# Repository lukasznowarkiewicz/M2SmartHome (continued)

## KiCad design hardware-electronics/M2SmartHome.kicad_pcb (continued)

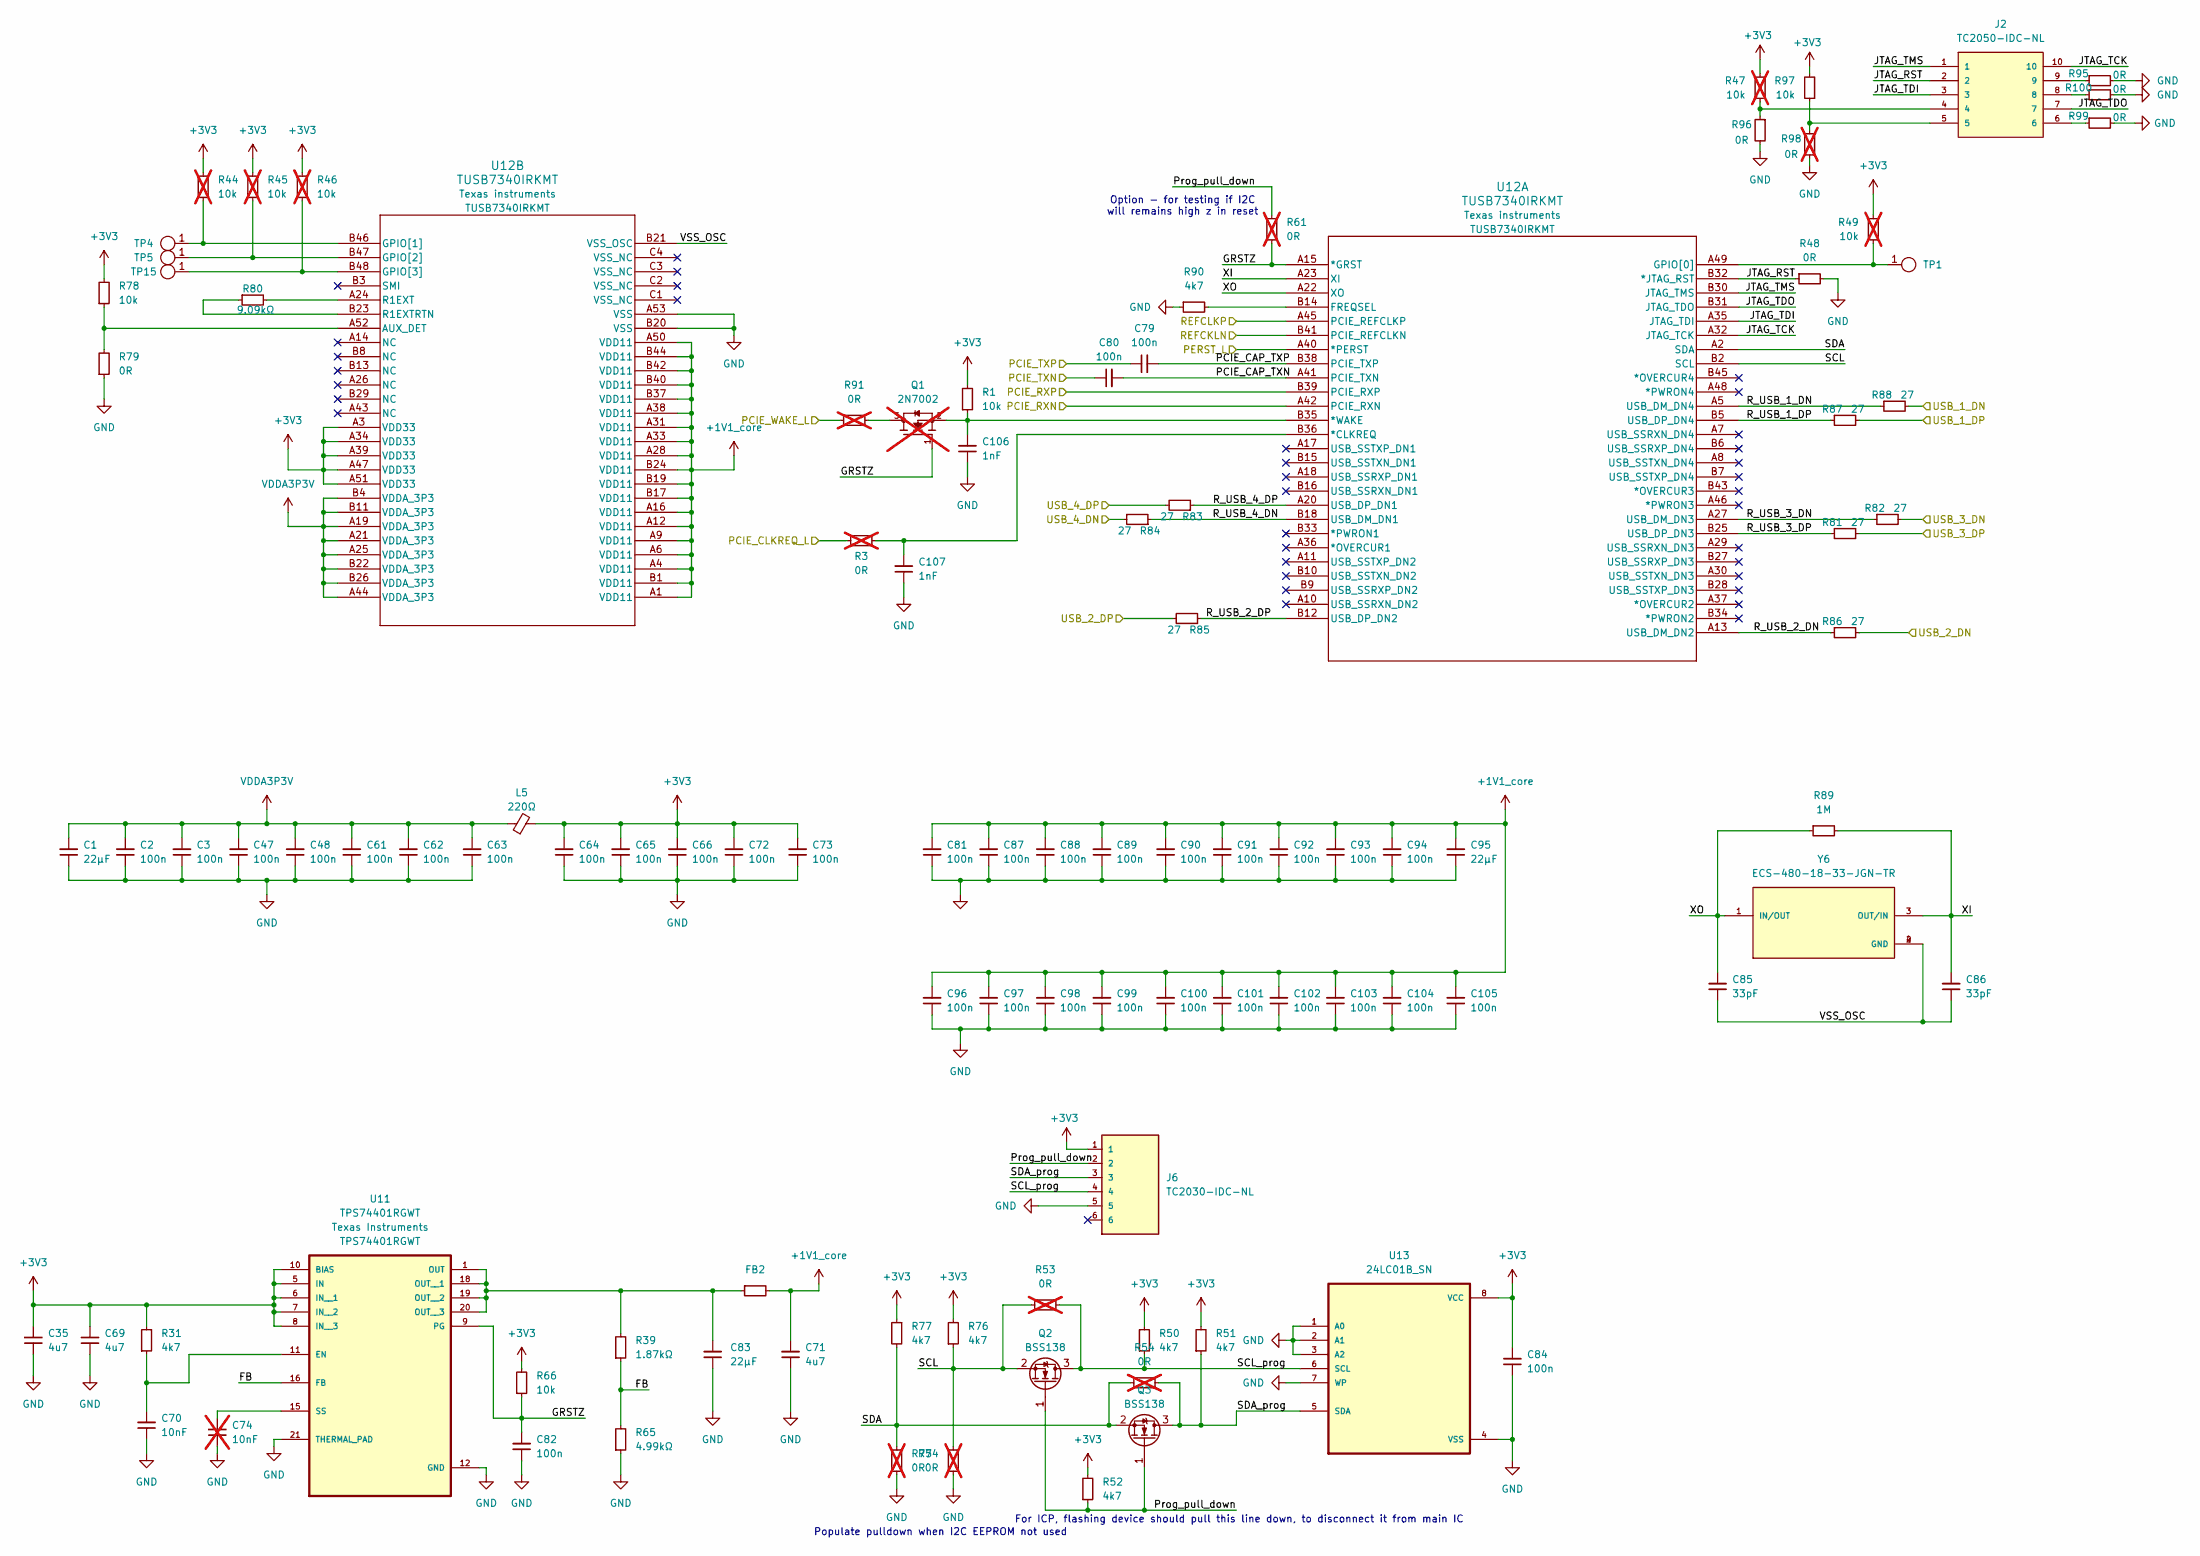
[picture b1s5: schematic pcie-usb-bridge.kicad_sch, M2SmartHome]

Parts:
C1, C83, C95: C_22uF_10pct_10V_0603_C1608X5R1A226M080AC; C_0603; MPN C1608X5R1A226M080AC
C2, C3, C47, C48, C61, C62, C63, C64, C65, C66, C72, C73, C79, C80, C81, C82, C84, C87, C88, C89, C90, C91, C92, C93, C94, C96, C97, C98, C99, C100, C101, C102, C103, C104, C105: C_100n_0402; C_0402; Voltage 10V; MPN GRM155R61A104KA01D
C35, C69, C71: C_4u7_0402; C_0402; Voltage 6.3V; MPN GRM155R60J475ME47D
C70: C_10nF_5pct_50V_0402_C0402C103J5RACTU; C_0402; MPN C0402C103J5RACTU
C74: C_10nF_5pct_50V_0402_C0402C103J5RACTU; C_0402; MPN C0402C103J5RACTU; not fitted
C85, C86: C_33pF_5pct_50V_0402_C1005NP01H330J050BA; C_0402; MPN C1005NP01H330J050BA
C106, C107: C_1nF_10pct_25V_0402_ KGM05AR71E102KH; C_0402; MPN KGM05AR71E102KH
FB2: FB_120R_0603; FB_0603; MPN BLM18AG121SN1D
J2: TC2050-IDC-NL; TAG-CONNECT_TC2050-IDC-NL; PARTREV A
J6: TC2030-IDC-NL; TAG_TC2030-IDC-NL; PARTREV MS
L5: FB_220Ohm_600mA_0805_BLM21PG221SN1D; FB_0805; MPN BLM21PG221SN1D
Q1: 2N7002; TRANS_2N7002; PARTREV 2023-01-11; not fitted
Q2, Q3: BSS138; SOT-23
R1, R66, R78, R97: R_10k_0402; R_0402; Tolerance 1%; MPN CRCW040210K0FKED
R3, R53, R54, R61, R74, R75, R91, R98: R_0_0402; R_0402; MPN CRCW04020000Z0ED; not fitted
R31, R50, R51, R52, R76, R77, R90: R_4k7_0402; R_0402; Tolerance 1%; MPN CRCW04024K70FKED
R39: R_1k87_1pct_0402_CRCW04021K87FKED; R_0402; MPN CRCW04021K87FKED
R44, R45, R46, R47, R49: R_10k_0402; R_0402; Tolerance 1%; MPN CRCW040210K0FKED; not fitted
R48, R79, R95, R96, R99, R100: R_0_0402; R_0402; MPN CRCW04020000Z0ED
R65: R_4k99_1pct_125mW_0402_CRCW04024K99FKEDHP; R_0402; MPN CRCW04024K99FKEDHP
R80: R_9k09_1pct_0402_CRCW04029K09FKED; R_0402; MPN CRCW04029K09FKED
R81, R82, R83, R84, R85, R86, R87, R88: R_27_0402; R_0402; Tolerance 1%; MPN CRCW040227R0FKED
R89: R_1M_0402; R_0402; Tolerance 1%; MPN CRCW04021M00FKED
TP1, TP4, TP5, TP15: TestPoint_Pad_D1.0mm
U11: TPS74401RGWT; MPN TPS74401RGWT
U12: TUSB7340IRKMT; MPN TUSB7340IRKMT
U13: 24LC01B_SN; MPN 24LC01B/SN
Y6: ECS-480-18-33-JGN-TR; MPN ECS-480-18-33-JGN-TR

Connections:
+1V1_core: C71.2, C81.2, C87.2, C88.2, C89.2, C90.2, C91.2, C92.2, C93.2, C94.2, C95.2, C96.2, C97.2, C98.2, C99.2, C100.2, C101.2, C102.2, C103.2, C104.2, C105.2, FB2.2, U12.A1 (VDD11), U12.A4 (VDD11), U12.A6 (VDD11), U12.A9 (VDD11), U12.A12 (VDD11), U12.A16 (VDD11), U12.A28 (VDD11), U12.A31 (VDD11), U12.A33 (VDD11), U12.A38 (VDD11), U12.A50 (VDD11), U12.B1 (VDD11), U12.B17 (VDD11), U12.B19 (VDD11), U12.B24 (VDD11), U12.B37 (VDD11), U12.B40 (VDD11), U12.B42 (VDD11), U12.B44 (VDD11)
+3V3: C35.2, C64.2, C65.2, C66.2, C69.2, C72.2, C73.2, C84.2, J6.1, L5.2, R1.2, R31.2, R44.2, R45.2, R46.2, R47.2, R49.2, R50.2, R51.2, R52.2, R66.2, R76.2, R77.1, R78.2, R97.2, U11.5 (IN), U11.6 (IN__1), U11.7 (IN__2), U11.8 (IN__3), U11.10 (BIAS), U12.A3 (VDD33), U12.A34 (VDD33), U12.A39 (VDD33), U12.A47 (VDD33), U12.A51 (VDD33), U13.8 (VCC); also elsewhere on the board
/PCIE.REFCLKN: U12.B41 (PCIE_REFCLKN); also elsewhere on the board
/PCIE.REFCLKP: U12.A45 (PCIE_REFCLKP); also elsewhere on the board
/PCIE.RXN: U12.A42 (PCIE_RXN); also elsewhere on the board
/PCIE.RXP: U12.B39 (PCIE_RXP); also elsewhere on the board
/PCIE.TXN: C80.1; also elsewhere on the board
/PCIE.TXP: C79.1; also elsewhere on the board
/emmc/USB_1_DN: R88.2; also elsewhere on the board
/emmc/USB_1_DP: R87.2; also elsewhere on the board
/pcie-usb-bridge/FB: R39.1, R65.2, U11.16 (FB)
/pcie-usb-bridge/GRSTZ: C82.2, Q1.1, R61.2, R66.1, U11.9 (PG), U12.A15 (*GRST)
/pcie-usb-bridge/JTAG_RST: J2.2, R48.1, U12.B32 (*JTAG_RST)
/pcie-usb-bridge/JTAG_TCK: J2.10, U12.A32 (JTAG_TCK)
/pcie-usb-bridge/JTAG_TDI: J2.3, U12.A35 (JTAG_TDI)
/pcie-usb-bridge/JTAG_TDO: J2.7, U12.B31 (JTAG_TDO)
/pcie-usb-bridge/JTAG_TMS: J2.1, U12.B30 (JTAG_TMS)
/pcie-usb-bridge/PCIE_CAP_TXN: C80.2, U12.A41 (PCIE_TXN)
/pcie-usb-bridge/PCIE_CAP_TXP: C79.2, U12.B38 (PCIE_TXP)
/pcie-usb-bridge/PCIE_CLKREQ_L: R3.1; also elsewhere on the board
/pcie-usb-bridge/PCIE_WAKE_L: R91.1; also elsewhere on the board
/pcie-usb-bridge/PERST_L: U12.A40 (*PERST); also elsewhere on the board
/pcie-usb-bridge/Prog_pull_down: J6.2, Q2.1 (G), Q3.1 (G), R52.1, R61.1
/pcie-usb-bridge/R_USB_1_DN: R88.1, U12.A5 (USB_DM_DN4)
/pcie-usb-bridge/R_USB_1_DP: R87.1, U12.B5 (USB_DP_DN4)
/pcie-usb-bridge/R_USB_2_DN: R86.1, U12.A13 (USB_DM_DN2)
/pcie-usb-bridge/R_USB_2_DP: R85.1, U12.B12 (USB_DP_DN2)
/pcie-usb-bridge/R_USB_3_DN: R82.1, U12.A27 (USB_DM_DN3)
/pcie-usb-bridge/R_USB_3_DP: R81.1, U12.B25 (USB_DP_DN3)
/pcie-usb-bridge/R_USB_4_DN: R84.1, U12.B18 (USB_DM_DN1)
/pcie-usb-bridge/R_USB_4_DP: R83.1, U12.A20 (USB_DP_DN1)
/pcie-usb-bridge/SCL: Q2.2 (S), R53.2, R74.2, R76.1, U12.B2 (SCL)
/pcie-usb-bridge/SCL_prog: J6.4, Q2.3 (D), R50.1, R53.1, U13.6 (SCL)
/pcie-usb-bridge/SDA: Q3.2 (S), R54.2, R75.2, R77.2, U12.A2 (SDA)
/pcie-usb-bridge/SDA_prog: J6.3, Q3.3 (D), R51.1, R54.1, U13.5 (SDA)
/pcie-usb-bridge/USB_2_DN: R86.2; also elsewhere on the board
/pcie-usb-bridge/USB_2_DP: R85.2; also elsewhere on the board
/pcie-usb-bridge/USB_3_DN: R82.2; also elsewhere on the board
/pcie-usb-bridge/USB_3_DP: R81.2; also elsewhere on the board
/pcie-usb-bridge/USB_4_DN: R84.2; also elsewhere on the board
/pcie-usb-bridge/USB_4_DP: R83.2; also elsewhere on the board
/pcie-usb-bridge/VSS_OSC: C85.1, C86.1, U12.B21 (VSS_OSC), Y6.2 (GND), Y6.4 (GND)
/pcie-usb-bridge/XI: C86.2, R89.2, U12.A23 (XI), Y6.3 (OUT/IN)
/pcie-usb-bridge/XO: C85.2, R89.1, U12.A22 (XO), Y6.1 (IN/OUT)
GND: C1.1, C2.1, C3.1, C35.1, C47.1, C48.1, C61.1, C62.1, C63.1, C64.1, C65.1, C66.1, C69.1, C70.1, C71.1, C72.1, C73.1, C74.1, C81.1, C82.1, C83.1, C84.1, C87.1, C88.1, C89.1, C90.1, C91.1, C92.1, C93.1, C94.1, C95.1, C96.1, C97.1, C98.1, C99.1, C100.1, C101.1, C102.1, C103.1, C104.1, C105.1, C106.1, C107.1, J6.5, R48.2, R65.1, R74.1, R75.1, R79.1, R90.1, R95.2, R96.2, R98.2, R99.2, R100.2, U11.12 (GND), U11.21 (THERMAL_PAD), U12.A53 (VSS), U12.B20 (VSS), U13.1 (A0), U13.2 (A1), U13.3 (A2), U13.4 (VSS), U13.7 (WP); also elsewhere on the board
unnamed: J2.4, R47.1, R96.1
unnamed: J2.5, R97.1, R98.1
unnamed: J2.6, R99.1
unnamed: J2.8, R100.1
unnamed: J2.9, R95.1
unnamed: Q1.3, R91.2
unnamed: C70.2, R31.1, U11.11 (EN)
unnamed: C83.2, FB2.1, R39.2, U11.1 (OUT), U11.18 (OUT__1), U11.19 (OUT__2), U11.20 (OUT__3)
unnamed: C74.2, U11.15 (SS)
unnamed: C107.2, R3.2, U12.B36 (*CLKREQ)
unnamed: C106.2, Q1.2, R1.1, U12.B35 (*WAKE)
unnamed: R90.2, U12.B14 (FREQSEL)
unnamed: R49.1, TP1.1, U12.A49 (GPIO[0])
unnamed: R78.1, R79.2, U12.A52 (AUX_DET)
unnamed: R44.1, TP4.1, U12.B46 (GPIO[1])
unnamed: R45.1, TP5.1, U12.B47 (GPIO[2])
unnamed: R46.1, TP15.1, U12.B48 (GPIO[3])
unnamed: R80.2, U12.A24 (R1EXT)
unnamed: R80.1, U12.B23 (R1EXTRTN)
VDDA3P3V: C1.2, C2.2, C3.2, C47.2, C48.2, C61.2, C62.2, C63.2, L5.1, U12.A19 (VDDA_3P3), U12.A21 (VDDA_3P3), U12.A25 (VDDA_3P3), U12.A44 (VDDA_3P3), U12.B4 (VDDA_3P3), U12.B11 (VDDA_3P3), U12.B22 (VDDA_3P3), U12.B26 (VDDA_3P3)

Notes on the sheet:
For ICP, flashing device should pull this line down, to disconnect it from main IC
Populate pulldown when I2C EEPROM not used
Option - for testing if I2C will remains high z in reset

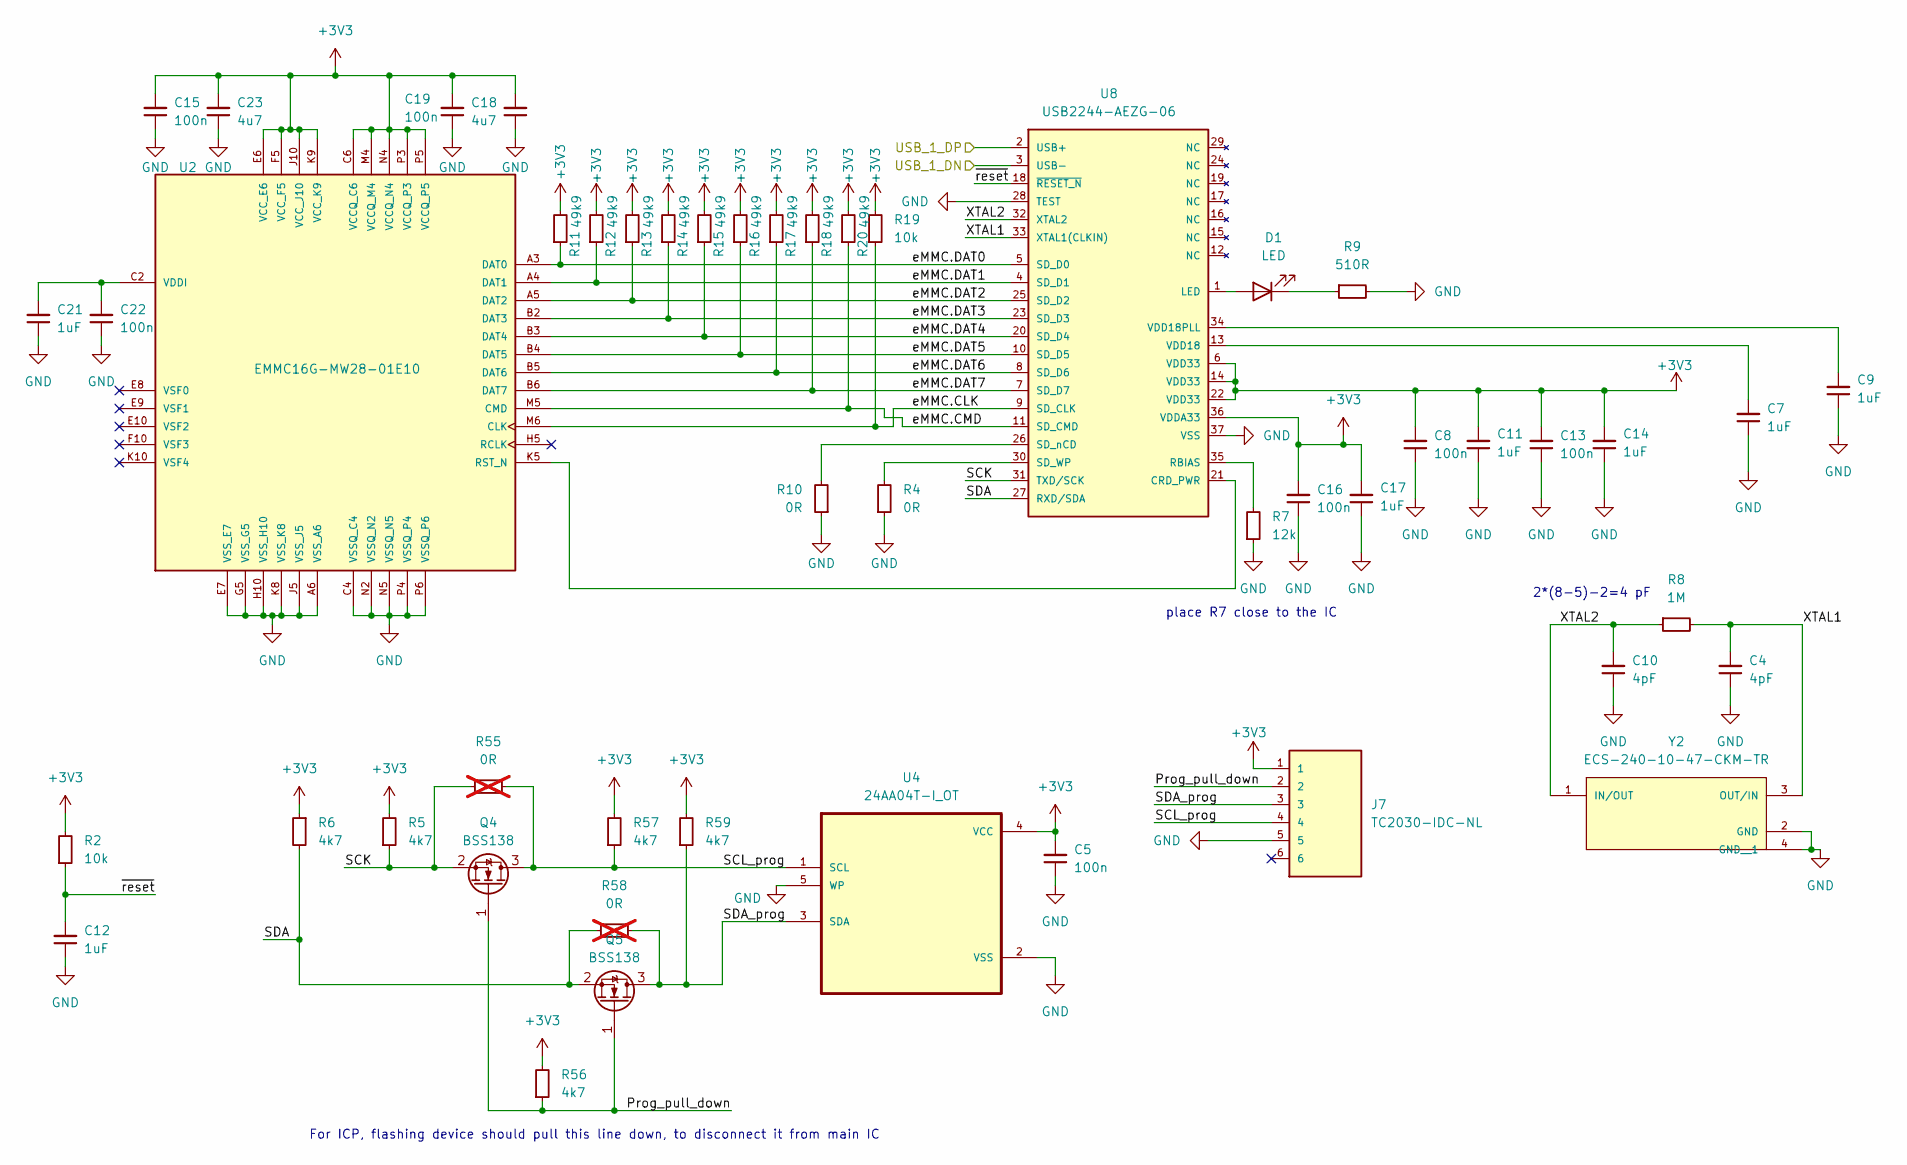
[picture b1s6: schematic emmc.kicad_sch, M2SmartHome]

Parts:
C4, C10: C_4pF_0402; C_0402; Voltage 50V; MPN GRM1555C1H4R0CA01D
C5, C8, C13, C15, C16, C19, C22: C_100n_0402; C_0402; Voltage 10V; MPN GRM155R61A104KA01D
C7, C9, C11, C12, C14, C17, C21: C_1uF_0402; C_0402; Voltage 50V; MPN GRM155R61H105KE05D
C18, C23: C_4u7_0402; C_0402; Voltage 6.3V; MPN GRM155R60J475ME47D
D1: LED; LED_KPT-1608ZGC
J7: TC2030-IDC-NL; TAG_TC2030-IDC-NL; PARTREV MS
Q4, Q5: BSS138; SOT-23
R2, R19: R_10k_0402; R_0402; Tolerance 1%; MPN CRCW040210K0FKED
R4, R10: R_0_0402; R_0402; MPN CRCW04020000Z0ED
R5, R6, R56, R57, R59: R_4k7_0402; R_0402; Tolerance 1%; MPN CRCW04024K70FKED
R7: R_12k_0402; R_0402; Tolerance 1%; Voltage 50V; MPN CRCW040212K0FKTDBC
R8: R_1M_0402; R_0402; Tolerance 1%; MPN CRCW04021M00FKED
R9: R_510R_0402; R_0402; Tolerance 1%; MPN CRCW0402510RJNED
R11, R12, R13, R14, R15, R16, R17, R18, R20: R_49k9_0402; R_0402; Tolerance 1%; MPN CRCW040249K9FKED
R55, R58: R_0_0402; R_0402; MPN CRCW04020000Z0ED; not fitted
U2: EMMC16G-MW28-01E10
U4: 24AA04T-I_OT
U8: USB2244-AEZG-06
Y2: ECS-240-10-47-CKM-TR; PARTREV 2017

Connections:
+3V3: C5.2, C8.2, C11.2, C13.2, C14.2, C15.2, C16.2, C17.2, C18.2, C19.2, C23.2, J7.1, R2.2, R5.2, R6.1, R11.2, R12.2, R13.2, R14.2, R15.2, R16.2, R17.2, R18.2, R19.2, R20.2, R56.2, R57.2, R59.2, U2.C6 (VCCQ_C6), U2.E6 (VCC_E6), U2.F5 (VCC_F5), U2.J10 (VCC_J10), U2.K9 (VCC_K9), U2.M4 (VCCQ_M4), U2.N4 (VCCQ_N4), U2.P3 (VCCQ_P3), U2.P5 (VCCQ_P5), U4.4 (VCC), U8.6 (VDD33), U8.14 (VDD33), U8.22 (VDD33), U8.36 (VDDA33); also elsewhere on the board
/emmc/Prog_pull_down: J7.2, Q4.1 (G), Q5.1 (G), R56.1
/emmc/SCK: Q4.2 (S), R5.1, R55.2, U8.31 (TXD/SCK)
/emmc/SCL_prog: J7.4, Q4.3 (D), R55.1, R57.1, U4.1 (SCL)
/emmc/SDA: Q5.2 (S), R6.2, R58.2, U8.27 (RXD/SDA)
/emmc/SDA_prog: J7.3, Q5.3 (D), R58.1, R59.1, U4.3 (SDA)
/emmc/USB_1_DN: U8.3 (USB-); also elsewhere on the board
/emmc/USB_1_DP: U8.2 (USB+); also elsewhere on the board
/emmc/XTAL1: C4.2, R8.2, U8.33 (XTAL1(CLKIN)), Y2.3 (OUT/IN)
/emmc/XTAL2: C10.2, R8.1, U8.32 (XTAL2), Y2.1 (IN/OUT)
/emmc/eMMC.CLK: R19.1, U2.M6 (CLK), U8.9 (SD_CLK)
/emmc/eMMC.CMD: R20.1, U2.M5 (CMD), U8.11 (SD_CMD)
/emmc/eMMC.DAT0: R11.1, U2.A3 (DAT0), U8.5 (SD_D0)
/emmc/eMMC.DAT1: R12.1, U2.A4 (DAT1), U8.4 (SD_D1)
/emmc/eMMC.DAT2: R13.1, U2.A5 (DAT2), U8.25 (SD_D2)
/emmc/eMMC.DAT3: R14.1, U2.B2 (DAT3), U8.23 (SD_D3)
/emmc/eMMC.DAT4: R15.1, U2.B3 (DAT4), U8.20 (SD_D4)
/emmc/eMMC.DAT5: R16.1, U2.B4 (DAT5), U8.10 (SD_D5)
/emmc/eMMC.DAT6: R17.1, U2.B5 (DAT6), U8.8 (SD_D6)
/emmc/eMMC.DAT7: R18.1, U2.B6 (DAT7), U8.7 (SD_D7)
/emmc/~reset: C12.2, R2.1, U8.18 (~RESET_N)
GND: C4.1, C5.1, C7.1, C8.1, C9.1, C10.1, C11.1, C12.1, C13.1, C14.1, C15.1, C16.1, C17.1, C18.1, C19.1, C21.1, C22.1, C23.1, J7.5, R4.1, R7.1, R9.2, R10.1, U2.A6 (VSS_A6), U2.C4 (VSSQ_C4), U2.E7 (VSS_E7), U2.G5 (VSS_G5), U2.H10 (VSS_H10), U2.J5 (VSS_J5), U2.K8 (VSS_K8), U2.N2 (VSSQ_N2), U2.N5 (VSSQ_N5), U2.P4 (VSSQ_P4), U2.P6 (VSSQ_P6), U4.2 (VSS), U4.5 (WP), U8.28 (TEST), U8.37 (VSS), Y2.2 (GND), Y2.4 (GND__1); also elsewhere on the board
unnamed: D1.2 (A), U8.1 (LED)
unnamed: D1.1 (K), R9.1
unnamed: U2.K5 (RST_N), U8.21 (CRD_PWR)
unnamed: C21.2, C22.2, U2.C2 (VDDI)
unnamed: R7.2, U8.35 (RBIAS)
unnamed: R4.2, U8.30 (SD_WP)
unnamed: R10.2, U8.26 (SD_nCD)
unnamed: C7.2, U8.13 (VDD18)
unnamed: C9.2, U8.34 (VDD18PLL)

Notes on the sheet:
For ICP, flashing device should pull this line down, to disconnect it from main IC
2*(8-5)-2=4 pF
place R7 close to the IC

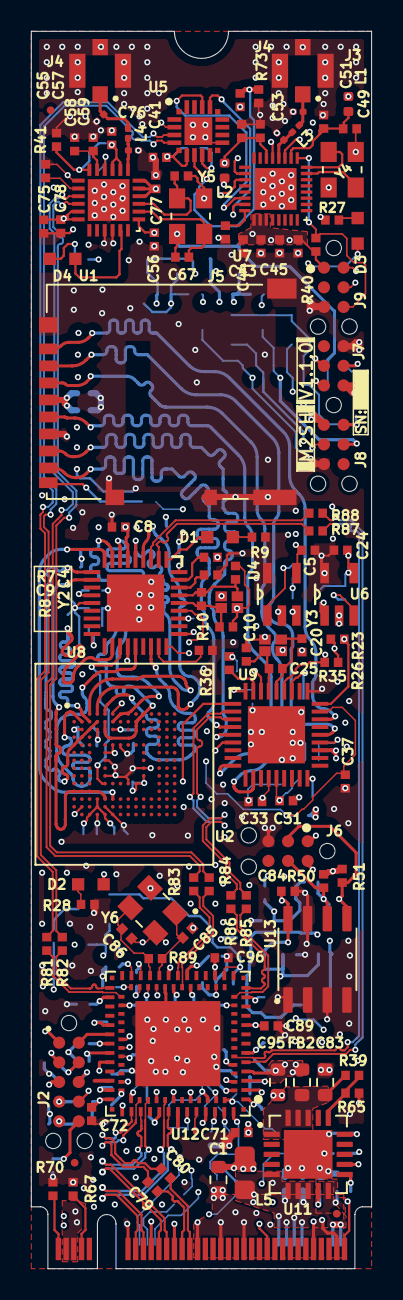
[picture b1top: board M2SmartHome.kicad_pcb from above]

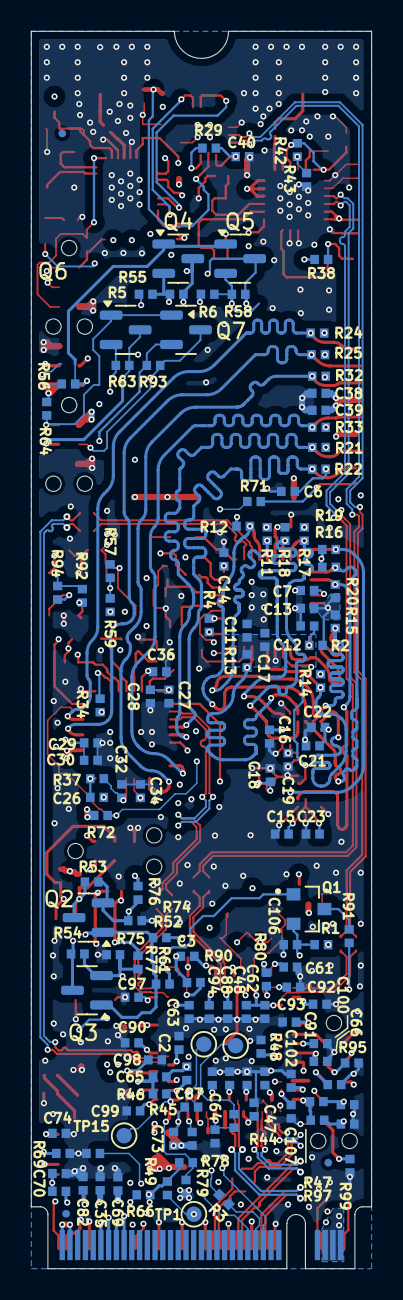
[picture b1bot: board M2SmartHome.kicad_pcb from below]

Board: 6 copper layers, 22.0 x 80.0 mm, 257 parts (143 on the bottom side), 143 nets.

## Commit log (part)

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2024-11-12 [#17] uSD data lines WIP
2024-11-13 [#17] SCH update USB net names
2024-11-13 [#17] uSD components connections
2024-11-13 [#17] Thread radio components connection WIP
2024-11-13 [#17] WiFi radio components connection WIP
2024-11-17 [#17] downsized all vias
2024-11-17 [#17] Chane stackup to JLC04081H-3313
2024-11-17 [#17] USB 2.0 routed for new stackup
2024-11-17 [#17] eMMC routing WIP
2024-11-17 [#17] uSD routing WIP
2024-11-20 [#17] eMMC moved by 0.8 mm
2024-11-20 [#17] eMMC routing after repositioning
2024-11-20 [#17] eMMC controller moved 1mm
2024-11-20 [#17] eMMC controller rerouting tracks after repositioning
2024-11-20 [#17] Resized designators
2024-11-20 [#17] Reposition designators top
2024-11-20 [#17] Reposition designators bottom
2024-11-20 [#17] Update copper planes
2024-11-20 [#17] PCIe bridge DCDC converter routing WI
2024-11-21 [#17] PCIe bridge DCDC converter routing
2024-11-21 [#17] PCIe bridge routing around WIP
2024-11-21 [#17] Moved everything 1 mm away from M.2 connector
2024-11-21 [#17] PCIe bridge routing around
2024-11-21 [#17] PCIe bridge matched lenght of PCIe lines
2024-11-21 [#17] Matched lenght of USB lines
2024-11-21 [#17] Routing uSD data lines WIP
2024-11-21 [#17] uSD data lines lenght matching WIP
2024-11-23 [#17] connecting unconneted nets WIP
2024-11-23 [#17] eMMC routing WIP set proper trace wthicknes to keep SE 50 ohm
2024-11-23 [#17] eMMC routing WIP removed unecessary cap
2024-11-23 [#17] eMMC and uSD routing WIP
2024-11-23 [#17] USB add cutouts and GND planes under resistors to keep impedance
2024-11-24 [#17] uSD lenght matching
2024-11-24 [#17] eMMC lenght matching WIP
2024-11-24 [#17] Change via hole to 0.25 mm
2024-11-24 [#17] WIFI UFL connector routing
2024-11-24 [#17] Thread routing
2024-11-25 [#17] Thread routing WIP
2024-11-25 [#17] USB routing WIP
2024-11-25 [#17] Add GND copper on F and B to equalize copper distrubution
2024-11-25 [#17] Working on power planes
2024-11-25 [#17] Thread routing, power planes
2024-11-25 [#18] SCH excluded ERC violations
2024-11-25 [#20] PCB cleanup WIP
2024-11-25 [#20] PCB DRC WIP
2024-11-25 [#20] PCB DRC WIP ignored all solder mask aperture bridges items with different nets
2024-11-25 [#20] PCB DRC WIP shortened uSD card pads
2024-11-25 [#20] PCB DRC WIP changed minimum track width to 0.1 mm
2024-11-25 [#20] PCB DRC WIP HS fanouts
2024-11-25 [#20] PCB DRC WIP USB lines fix
2024-11-25 [#20] PCB DRC WIP check with JLCPCB viewer
2024-11-26 [#20] PCB DRC warnings WIP excluded all text height violations
2024-11-26 [#20] PCB DRC warnings WIP placing desginators
2024-11-26 [#20] PCB DRC warnings WIP placing desginators, fixing footptints
2024-11-26 [#20] PCB DRC warnings WIP fix missing footprints
2024-11-26 [#20] PCB DRC warnings fix
2024-11-26 [#20] PCB DRC errors under eMMC
2024-11-26 [#20] PCB corrected mounting hole cutour according to PCIe sig specification
2024-11-26 [#20] PCB correct internal planes under edge connector according to figure 97 in PCIe M.2 electromechacnial specification
2024-11-26 [#20] PCB minor corrections
2024-11-26 [#20] PCB excluded DRC errors under eMMC
2024-11-26 [#20] PCB fix unconnected items
2024-11-26 [#20] PCB lenght matching eMMC WIP
2024-11-26 [#20] PCB lenght matched eMMC
2024-11-26 [#20] PCB exclude DRC errors related to eMMC
2024-11-26 [#20] PCB lenght match uSD
2024-11-26 [#20] PCB lenght match USB
2024-11-26 [#20] PCB fix tracks connected to uSD slot
2024-11-26 [#20] PCB add planes cutouts on vias on USB tracks
2024-11-26 [#20] PCB add vias near UFL connectors
2024-11-26 [#20] PCB add cap on pcie bridge pin 33
2024-11-26 [#20] PCB fix track on eMMC memory & fix DRC
2024-11-26 [#20] PCB add pullup filtration cap on uSD datalines
2024-11-26 [#20] PCB fix DRC
2024-11-26 [#20] PCB lenght match fix
2024-11-27 [#20] PCB repour polygons
2024-11-27 [#20] PCB minor fixes
2024-12-01 Add order files
2024-12-01 Add WIP sourcing document - add LCSC parts
2024-12-01 Add WIP sourcing document - add Mouser and Digikey parts
2025-01-14 [#24] Add symbol for TUSB7340IRKMT
2025-01-14 [#24] Add footprint and 3d model for TUSB7340IRKMT
2025-01-14 [#24] Add TUSB7340IRKMT to PCB (mockip)
2025-01-14 [#24] Update TUSB7340IRKMT footprint
2025-01-15 [#24] Add ECS-480-8-33B-CWN-TR
2025-01-15 [#24] Update ECS-480-8-33B-CWN-TR
2025-01-15 [#24] Add TPS74401RGWT
2025-01-15 [#24] Add 24LC01B_SN
2025-01-15 [#24] Add C1608X5R1A226M080AC
2025-01-15 [#24] Add BLM21PG221SN1D
2025-01-15 [#24] Add CRCW04029K09FKED
2025-01-15 [#24] Add CRCW04021K87FKED
2025-01-15 [#24] Add CRCW04024K99FKEDHP
2025-01-15 [#24] Add C0402C103J5RACTU
2025-01-15 [#24] SCH 1V1 LDO WIP
2025-01-15 [#24] SCH 1V1 LDO
2025-01-15 [#24] SCH I2C EEPROM
2025-01-15 [#24] SCH connect power part of TUSB7340IRKMT
2025-01-15 [#24] Add ECS-480-18-33-JGN-TR
2025-01-15 [#24] Add C1005NP01H330J050BA
2025-01-15 [#24] SCH add oscillator for TUSB7340IRKMT
2025-01-15 [#24] SCH add USB connections to TUSB7340IRKMT
2025-01-15 [#24] SCH add PCIe connections to TUSB7340IRKMT
2025-01-25 [#25] Add step model for CONMHF1-SMD-T
2025-01-25 [#25] Add step model for RTL8188FTV-VC-CG
2025-01-25 [#25] Add step model for ABM8-40.000MHZ-B2-T
2025-01-25 [#25] Add step model for ABM8-38.400MHZ-10-D1G-T
2025-01-25 [#25] Add step model for KPT-1608ZGC
2025-01-25 [#25] Add step model for 24AA04T-I/OT
2025-01-25 [#25] Add step model for XTAL_ABM8-12.000MHZ-B2-T
2025-01-25 [#25] Add step model for TPS62822DLCR
2025-01-25 [#25] Add step model for XFL4015-471MEC
2025-01-25 [#25] Update board
2025-01-25 [#25] Update board add missing TPS
2025-01-26 Add renders of the board
2025-01-29 Add assembly render
2025-01-29 Remove old docs export pipeline
2025-01-29 Add renders and image
2025-01-29 Add board views to README
2025-01-29 Add schematic to README
2025-01-29 Describe schematic in README
2025-01-29 Add board renders
2025-01-29 Readme Board bringup - PCIe bridge
2025-01-29 Readme Board bringup - eMMC memory
2025-01-29 Readme Board bringup - uSD reader
2025-01-29 Readme - add rev
2025-01-29 Restore design files from commit 30c85d8
2025-01-29 Add info about develop branch
2025-03-11 [#24] SCH Pcie bridge Cleanup
2025-03-11 [#24] SCH Pcie bridge add power filtration
2025-03-11 [#24] SCH Pcie bridge WAKE and CLKREQ signals
2025-03-12 [#24] SCH Pcie bridge fix footprint paths
2025-03-12 [#24] PCB Pcie bridge placement WIP
2025-03-13 [#24] PCB Pcie bridge placement
2025-03-13 [#24] PCB tag-connect programming connectors brainstorming
2025-03-17 [#26] Correct TX/RX PCIe line swap
2025-03-17 [#26] PCIe routing WIP
2025-03-18 [#26] Changed stackup to 6 layers JLC06081H-2116
2025-03-18 [#26] Update PCIe DP rules
2025-03-18 [#26] Update USB DP rules and ref plane openings
2025-03-18 [#26] Update PCIe DP rules to match 85ohm and ref plane openings
2025-03-18 [#26] Add more Vias under RF chips
2025-03-18 [#26] Add cutout and ref plane under U.FL connectors
2025-03-18 [#26] Fix mounting screw and screwhead opening
2025-03-19 [#26] Fix power planes on internal layers after updating stackup
2025-03-19 [#26] Pcie bridge HS fanout
2025-03-19 [#24] Pcie bridge vias for power supply
2025-03-19 [#24] Pcie bridge oscillator routing
2025-03-19 [#24] Pcie bridge decoupling capacitors routing
2025-03-20 [#26] Remove power plane splits for invidual devices
2025-03-20 [#26] Add programing interface for I2c devices
2025-03-20 [#26] Add programing interface for silicon labs MCU
2025-03-24 [#27] Add BOM for rev 1.1.0
2025-03-24 [#26] Correct MPN GRM155R61A104KA01D
2025-03-24 [#26] Correct MPN GRM155R61H105KE05D
2025-03-24 [#26] Correct MPN GRM1555C1H120GA01D
2025-03-24 [#26] Replace 500ohm to 510ohm MPN CRCW0402510RJNED
2025-03-25 [#26] Add I2C EEPROM for PCIe bridge ICP
2025-03-25 [#26] Add I2C EEPROM for emmc and usd ICP
2025-03-25 [#26] Add JTAG for pcie bridge
2025-03-25 [#26] PCB route PCIE jtag
2025-03-25 [#26] Fix connections to TC2030 I2C
2025-03-25 [#26] I2C prog pcie bridge routing WIP
2025-03-26 [#26] PCB route I2C for eMMC and uSD
2025-03-26 [#26] PCB improve routing I2C for eMMC and uSD
2025-03-27 [#26] PCB PCIe routing WIP
2025-03-27 [#26] PCB LDO routing WIP
2025-03-27 [#26] PCB routing WIP
2025-03-27 [#26] PCB routing WIP power planes under pcie bridge
2025-03-27 [#26] PCB routing WIP DRC
2025-03-30 [#26] PCB routing USB
2025-03-30 [#26] PCB save SE impedance for eMMC and uSD, eMMC routing WIP
2025-03-30 [#26] PCB eMMC lenght matching WIP
2025-03-30 [#26] PCB uSD routing WIP
2025-03-31 [#26] PCB uSD lenght matched
2025-03-31 [#26] PCB uSD rounded tracks
2025-03-31 [#26] PCB eMMC matched lenght
2025-03-31 [#26] PCB eMMC rounded tracks
2025-03-31 [#26] PCB platcing designator on B
2025-03-31 [#26] PCB improve routing
2025-03-31 [#26] PCB rounted USB 2.0 tracks
2025-03-31 [#26] PCB revert rounted USB 2.0 tracks
2025-03-31 [#26] PCB USB 2.0 improve impedance on resistors
2025-04-01 [#26] PCB DRC Errors WIP
2025-04-01 [#26] PCB lenght matched rounded eMMC signals
2025-04-01 [#26] PCB lenght matched rounded uSD signals
2025-04-01 [#26] PCB clear DRC errors
2025-04-01 [#26] PCB DRC warning WIP
2025-04-02 [#26] PCB lenght matched USB 2.0
2025-04-02 [#26] PCB lenght matched PCIe
2025-04-02 [#26] PCB clear DRC warnings
2025-04-02 [#26] PCB minor fixes
2025-04-02 [#26] PCIe bridge add USB die lenght
2025-04-02 [#26] PCIe bridge add PCIe die lenght
2025-04-02 [#26] PCB clean DRC
2025-04-02 [#26] PCB improve RBias routing
2025-04-02 [#26] PCB add fiducials, clean DRC
2025-04-02 [#26] PCB improve PCIe vias impedance
2025-04-02 [#26] PCB fix 0.09 mm tracks
2025-04-02 [#26] PCB fix pad spacing
2025-04-03 [#26] PCB add more stiching vias under IC, clean DRC
2025-05-28 Fix LQG15HS9N1J02D footprint
2025-05-28 Fix L1 and L2
2025-05-28 Populate R30
2025-05-28 Fix ferrite beads symbols
2025-05-28 TC2030-IDC-NL exclude from BOM
2025-05-28 M.2-Key-M-edge-connector exclude from BOM
2025-05-28 TC2050-IDC-NL exclude from BOM
2025-05-28 ECS-240-10-47-CKM-TR add MPN
2025-05-28 DM3AT-SF-PEJM5 add MPN
2025-05-28 Schematic cosmetic changes
2025-05-28 Schematic cleanup
2025-05-28 Add TUSB7340IRKMT missing step model
2025-05-28 Add BLM21PG221SN1D missing step model
2025-05-28 Readme rev 1.1.0 WIP
2025-06-05 Thread radio - fix decouple pin connection
2025-06-05 Add README section and firmware for customizing USB2240
2025-06-05 Readme - bringup procedure description, PCIe bringup
2025-06-05 README eMMC bringup
2025-06-05 README uSD bringup
2025-06-06 Readme bringup thread section
2025-06-06 Readme bringup wifi section
2025-06-06 Readme add USB2240 programming instruction
2025-06-08 Readme add EFR32 flashing section
2025-06-08 Readme move EFR32 flashing section
2025-06-08 Readme add modifications section
2025-06-08 UART add RTS/CTS signals
2025-06-09 Clean ERC, DRC, bump revision to 1.1.1
2025-06-09 README add missing images
2025-07-12 Add asprogrammer software
2025-07-12 Add thermal images
